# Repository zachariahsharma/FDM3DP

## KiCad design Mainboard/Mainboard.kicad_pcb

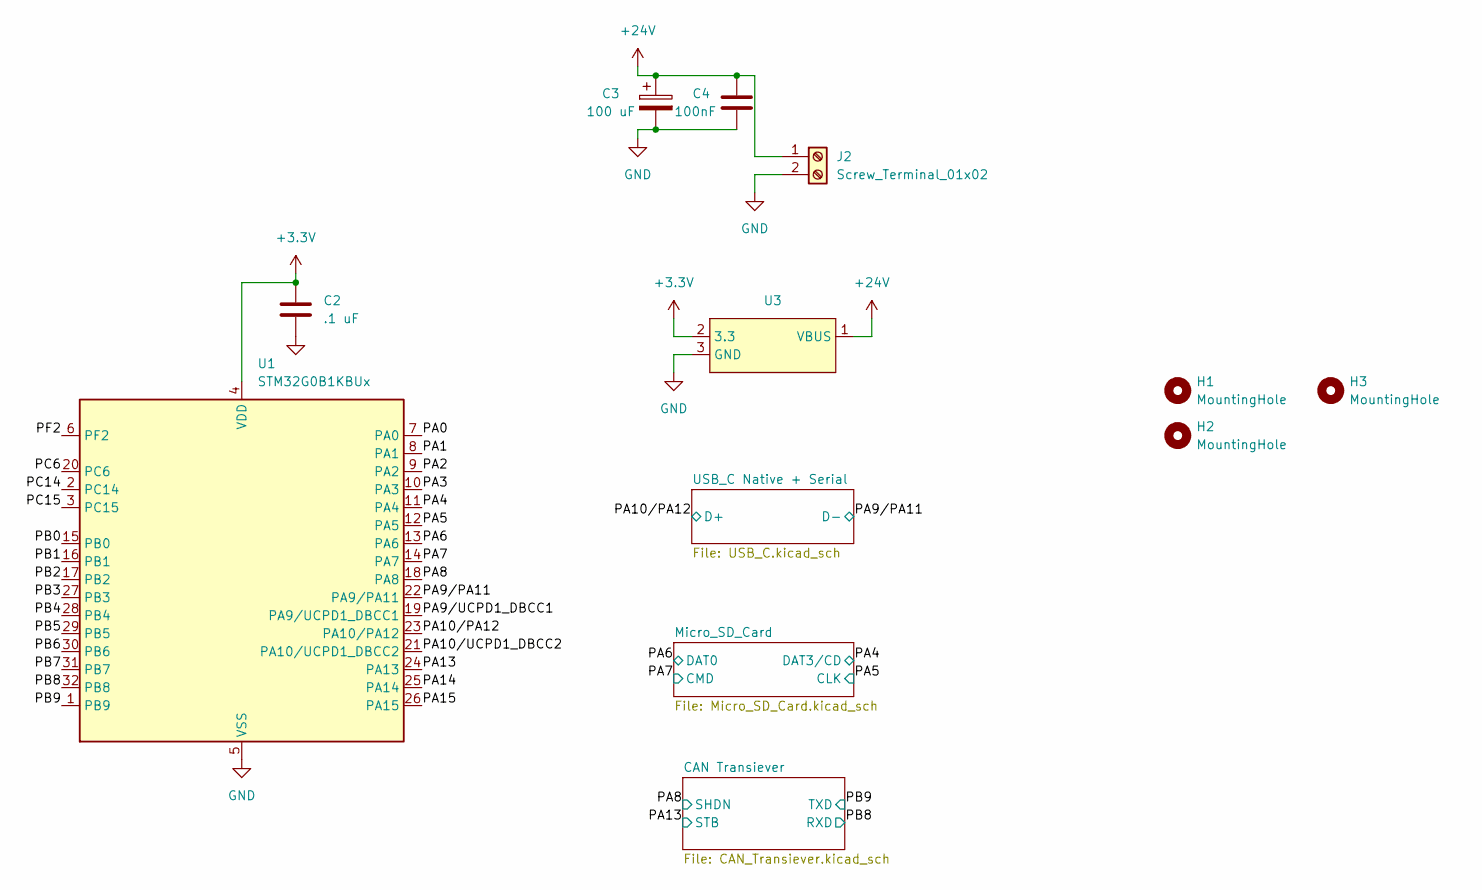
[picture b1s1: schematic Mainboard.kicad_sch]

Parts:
C2: .1 uF; C_0402_1005Metric; MPN GRM155R71C104KA88J
C3: 100 uF; CP_Radial_D8.0mm_P3.50mm; MPN 50ZLH100MEFC8X11.5
C4: 100nF; C_0402_1005Metric; MPN GRM155R71C104KA88J
H1, H2, H3: MountingHole; MountingHole_3mm
J2: Screw_Terminal_01x02; TerminalBlock_Phoenix_MKDS-1,5-2-5.08_1x02_P5.08mm_Horizont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; MPN 1715022
U1: STM32G0B1KBUx; QFN-32-1EP_5x5mm_P0.5mm_EP3.45x3.45mm; MPN STM32G0B1KBU6N
U3: Mini MP1584EN Buck Converter Module

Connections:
+3.3V: C2.1, U1.4 (VDD), U3.2 (3.3); also elsewhere on the board
+24V: C3.1, C4.1, J2.1, U3.1 (VBUS)
/PA0: U1.7 (PA0)
/PA1: U1.8 (PA1)
/PA2: U1.9 (PA2)
/PA3: U1.10 (PA3)
/PA4: U1.11 (PA4); also elsewhere on the board
/PA5: U1.12 (PA5); also elsewhere on the board
/PA6: U1.13 (PA6); also elsewhere on the board
/PA7: U1.14 (PA7); also elsewhere on the board
/PA8: U1.18 (PA8); also elsewhere on the board
/PA9/PA11: U1.22 (PA9/PA11); also elsewhere on the board
/PA9/UCPD1_DBCC1: U1.19 (PA9/UCPD1_DBCC1)
/PA10/PA12: U1.23 (PA10/PA12); also elsewhere on the board
/PA10/UCPD1_DBCC2: U1.21 (PA10/UCPD1_DBCC2)
/PA13: U1.24 (PA13); also elsewhere on the board
/PA14: U1.25 (PA14)
/PA15: U1.26 (PA15)
/PB0: U1.15 (PB0)
/PB1: U1.16 (PB1)
/PB2: U1.17 (PB2)
/PB3: U1.27 (PB3)
/PB4: U1.28 (PB4)
/PB5: U1.29 (PB5)
/PB6: U1.30 (PB6)
/PB7: U1.31 (PB7)
/PB8: U1.32 (PB8); also elsewhere on the board
/PB9: U1.1 (PB9); also elsewhere on the board
/PC6: U1.20 (PC6)
/PC14: U1.2 (PC14)
/PC15: U1.3 (PC15)
/PF2: U1.6 (PF2)
GND: C2.2, C3.2, C4.2, J2.2, U1.5 (VSS), U1.33 (VSS), U3.3 (GND); also elsewhere on the board

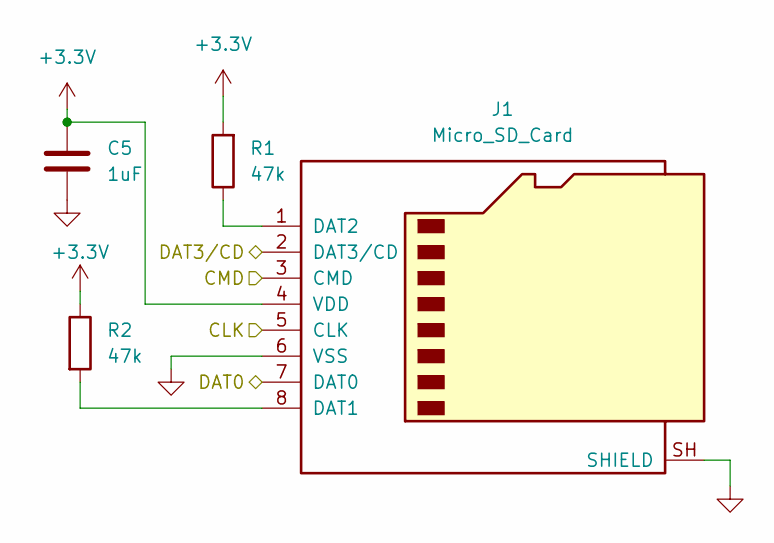
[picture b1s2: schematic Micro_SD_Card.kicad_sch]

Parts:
C5: 1uF; C_0805_2012Metric; MPN C0805C105K3RACTU
J1: Micro_SD_Card; microSD_HC_Hirose_DM3AT-SF-PEJM5; MPN DM3AT-SF-PEJM5
R1, R2: 47k; R_0402_1005Metric; MPN RC0402FR-0747KL

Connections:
+3.3V: C5.1, J1.4 (VDD), R1.2, R2.1; also elsewhere on the board
/PA4: J1.2 (DAT3/CD); also elsewhere on the board
/PA5: J1.5 (CLK); also elsewhere on the board
/PA6: J1.7 (DAT0); also elsewhere on the board
/PA7: J1.3 (CMD); also elsewhere on the board
GND: C5.2, J1.6 (VSS), J1.SH (SHIELD); also elsewhere on the board
unnamed: J1.8 (DAT1), R2.2
unnamed: J1.1 (DAT2), R1.1

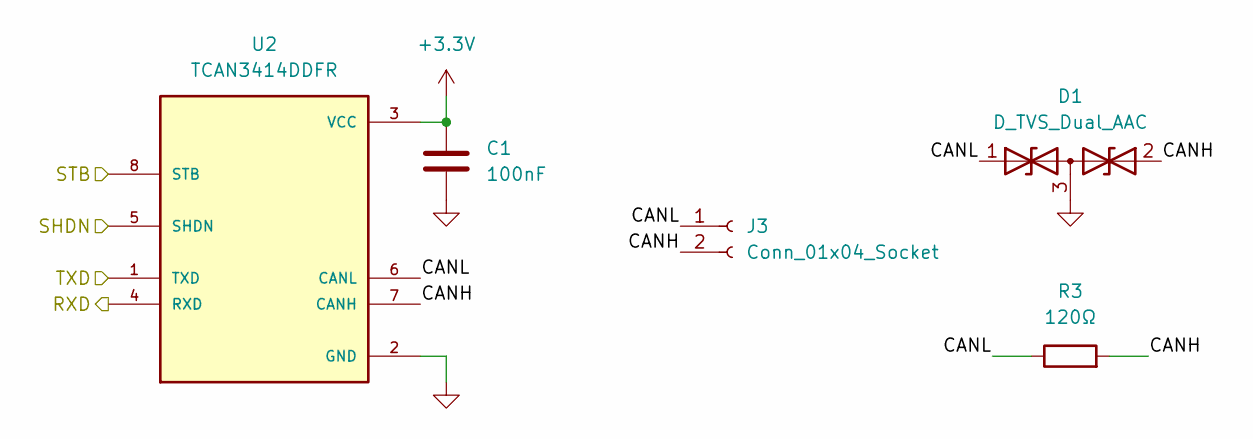
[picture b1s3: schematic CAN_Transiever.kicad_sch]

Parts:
C1: 100nF; C_0402_1005Metric; MPN GRM155R71C104KA88J
D1: D_TVS_Dual_AAC; SOT-23; MPN NUP2105LT1G
J3: Conn_01x04_Socket; PhoenixContact_MC_1,5_2-G-3.5_1x02_P3.50mm_Horizontal; MPN 1843990
R3: 120Ω; R_0402_1005Metric; MPN RC0402FR-07120RL
U2: TCAN3414DDFR; TSOT-23-8; MPN TCAN3414DDFR

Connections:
+3.3V: C1.1, U2.3 (VCC); also elsewhere on the board
/CAN Transiever/CANH: D1.2 (A2), J3.2, R3.2, U2.7 (CANH)
/CAN Transiever/CANL: D1.1 (A1), J3.1, R3.1, U2.6 (CANL)
/PA8: U2.5 (SHDN); also elsewhere on the board
/PA13: U2.8 (STB); also elsewhere on the board
/PB8: U2.4 (RXD); also elsewhere on the board
/PB9: U2.1 (TXD); also elsewhere on the board
GND: C1.2, D1.3 (common), U2.2 (GND); also elsewhere on the board

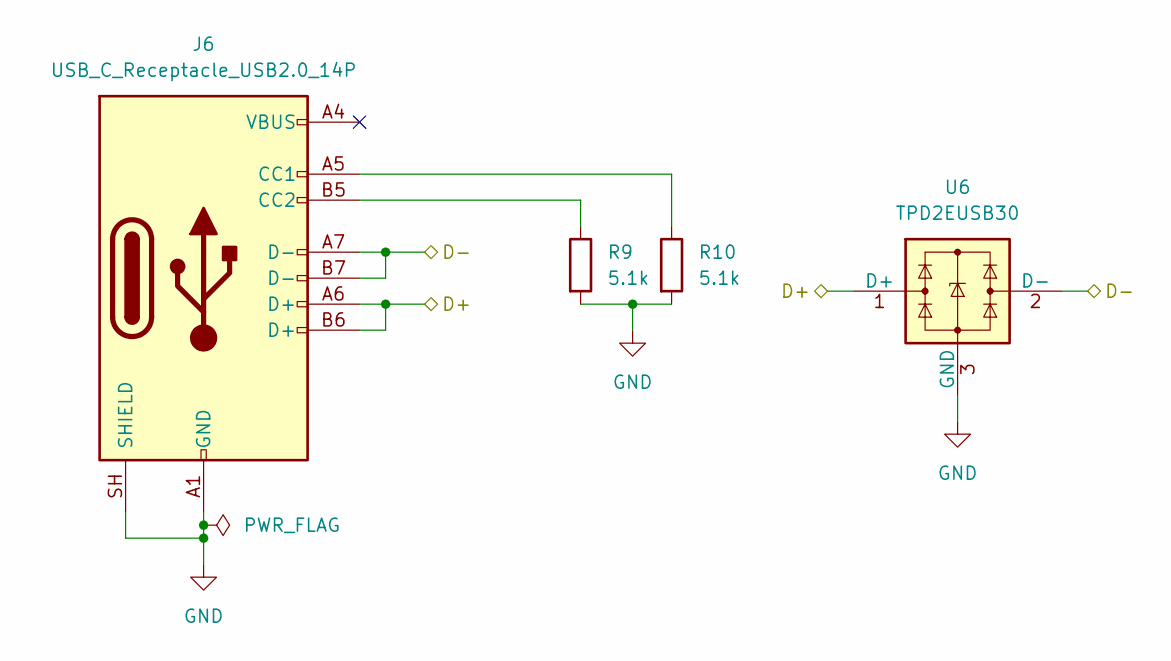
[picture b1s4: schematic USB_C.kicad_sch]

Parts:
J6: USB_C_Receptacle_USB2.0_14P; USB_C_Receptacle_GCT_USB4085; MPN USB4085-GF-A
R9, R10: 5.1k; R_0402_1005Metric; MPN RC0402FR-075K1L
U6: TPD2EUSB30; Texas_DRT-3; MPN TPD2EUSB30DRTR

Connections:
/PA9/PA11: J6.A7 (D-), J6.B7 (D-), U6.2 (D-); also elsewhere on the board
/PA10/PA12: J6.A6 (D+), J6.B6 (D+), U6.1 (D+); also elsewhere on the board
GND: J6.A1 (GND), J6.A12 (GND), J6.B1 (GND), J6.B12 (GND), J6.SH (SHIELD), R9.2, R10.2, U6.3 (GND); also elsewhere on the board
unnamed: J6.A5 (CC1), R10.1
unnamed: J6.B5 (CC2), R9.1

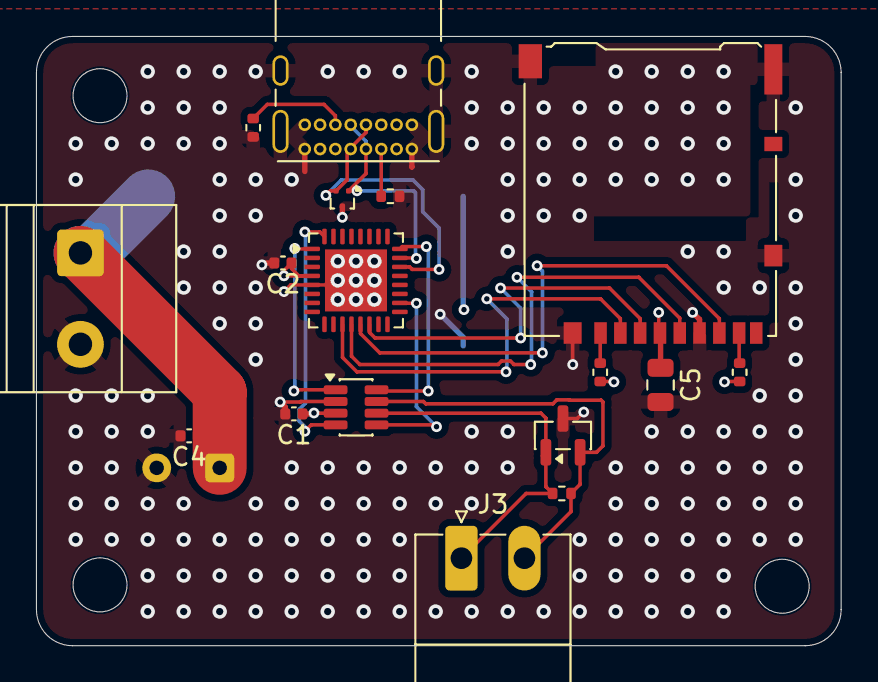
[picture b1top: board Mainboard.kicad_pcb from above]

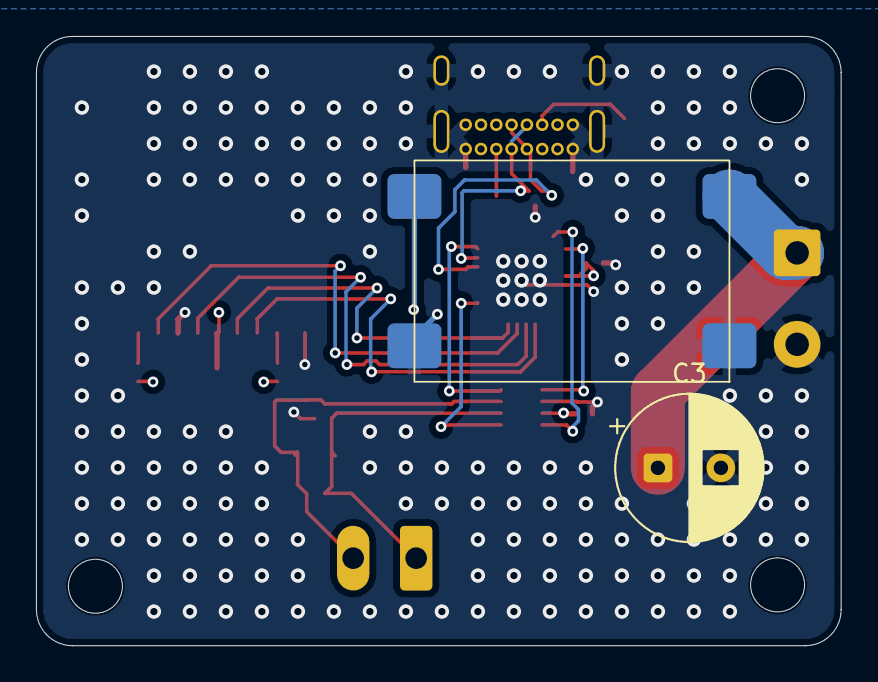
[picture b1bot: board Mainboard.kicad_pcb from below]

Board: 4 copper layers, 44.7 x 33.8 mm, 22 parts (2 on the bottom side), 19 nets.

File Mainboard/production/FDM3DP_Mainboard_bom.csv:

Designator,Footprint,Quantity,Value,LCSC Part #
"C1, C4",0402,2,100nF,KAM05FR71H104KH
C2,0402,1,.1 uF,KAM05FR71H104KH
C3,CP_Radial_D8.0mm_P3.50mm,1,100 uF,50ZLH100MEFC8X11.5
C5,0805,1,1uF,C0805C105K3RACTU
D1,SOT-23,1,D_TVS_Dual_AAC,NUP2105LT1G
J1,microSD_HC_Hirose_DM3AT-SF-PEJM5,1,Micro_SD_Card,DM3AT-SF-PEJM5
J2,"TerminalBlock_Phoenix_MKDS-1,5-2-5.08_1x02_P5.08mm_Horizontal",1,Screw_Terminal_01x02,1715022
J3,"PhoenixContact_MC_1,5_2-G-3.5_1x02_P3.50mm_Horizontal",1,Conn_01x04_Socket,1843990
J6,USB_C_Receptacle_GCT_USB4085,1,USB_C_Receptacle_USB2.0_14P,USB4085-GF-A
"R1, R2",0402,2,47k,RC0402FR-0747KL
"R10, R9",0402,2,5.1k,RC0402FR-075K1L
R3,0402,1,120Ω,RC0402FR-07120RL
U1,QFN-32-1EP_5x5mm_P0.5mm_EP3.45x3.45mm,1,STM32G0B1KBUx,STM32G0B1KBU6N
U2,TSOT-23-8,1,TCAN3414DDFR,TCAN3414DDFR
U3,Mini MP1584EN Buck Converter Module,1,~,
U6,Texas_DRT-3,1,TPD2EUSB30,TPD2EUSB30DRTR

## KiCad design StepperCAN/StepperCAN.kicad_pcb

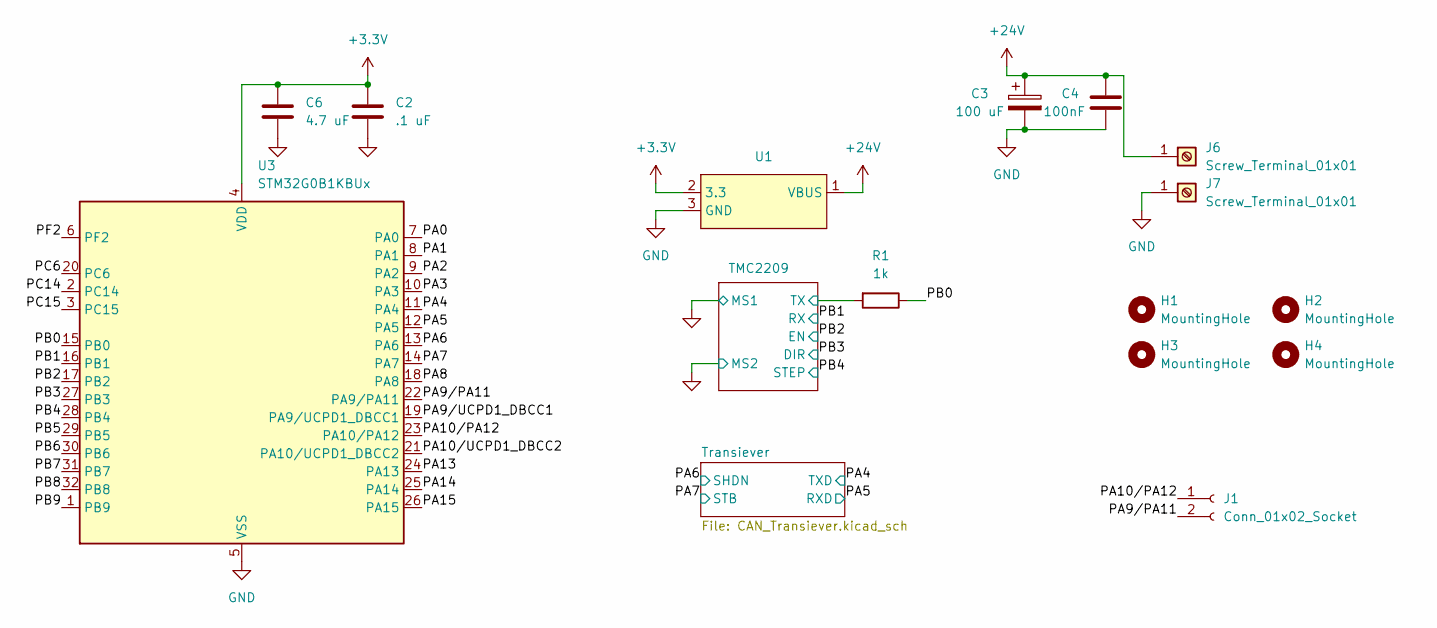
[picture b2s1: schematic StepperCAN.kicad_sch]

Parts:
C2: .1 uF; C_0402_1005Metric; MPN GRM155R71C104KA88J
C3: 100 uF; CP_Radial_D8.0mm_P3.50mm; MPN 50ZLH100MEFC8X11.5
C4: 100nF; C_0402_1005Metric; MPN GRM155R71C104KA88J
C6: 4.7 uF; C_0402_1005Metric; MPN CL05A475MO5NUNC
H1, H2, H3, H4: MountingHole; MountingHole_2.7mm_M2.5
J1: Conn_01x02_Socket; PinSocket_1x02_P2.54mm_Vertical
J6, J7: Screw_Terminal_01x01; M3 Screw Terminal
R1: 1k; R_0402_1005Metric; MPN RC0402FR-071KL
U1: Mini MP1584EN Buck Converter Module
U3: STM32G0B1KBUx; QFN-32-1EP_5x5mm_P0.5mm_EP3.45x3.45mm; MPN STM32G0B1KBU6N

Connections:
+3.3V: C2.1, C6.1, U1.2 (3.3), U3.4 (VDD); also elsewhere on the board
+24V: C3.1, C4.1, J6.1 (Pin_1_1), U1.1 (VBUS); also elsewhere on the board
/PA0: U3.7 (PA0)
/PA1: U3.8 (PA1)
/PA2: U3.9 (PA2)
/PA3: U3.10 (PA3)
/PA4: U3.11 (PA4); also elsewhere on the board
/PA5: U3.12 (PA5); also elsewhere on the board
/PA6: U3.13 (PA6); also elsewhere on the board
/PA7: U3.14 (PA7); also elsewhere on the board
/PA8: U3.18 (PA8)
/PA9/PA11: J1.2, U3.22 (PA9/PA11)
/PA9/UCPD1_DBCC1: U3.19 (PA9/UCPD1_DBCC1)
/PA10/PA12: J1.1, U3.23 (PA10/PA12)
/PA10/UCPD1_DBCC2: U3.21 (PA10/UCPD1_DBCC2)
/PA13: U3.24 (PA13)
/PA14: U3.25 (PA14)
/PA15: U3.26 (PA15)
/PB0: R1.1, U3.15 (PB0)
/PB1: R1.2, U3.16 (PB1); also elsewhere on the board
/PB2: U3.17 (PB2); also elsewhere on the board
/PB3: U3.27 (PB3); also elsewhere on the board
/PB4: U3.28 (PB4); also elsewhere on the board
/PB5: U3.29 (PB5)
/PB6: U3.30 (PB6)
/PB7: U3.31 (PB7)
/PB8: U3.32 (PB8)
/PB9: U3.1 (PB9)
/PC6: U3.20 (PC6)
/PC14: U3.2 (PC14)
/PC15: U3.3 (PC15)
/PF2: U3.6 (PF2)
GND: C2.2, C3.2, C4.2, C6.2, J7.1 (Pin_1_1), U1.3 (GND), U3.5 (VSS), U3.33 (VSS); also elsewhere on the board

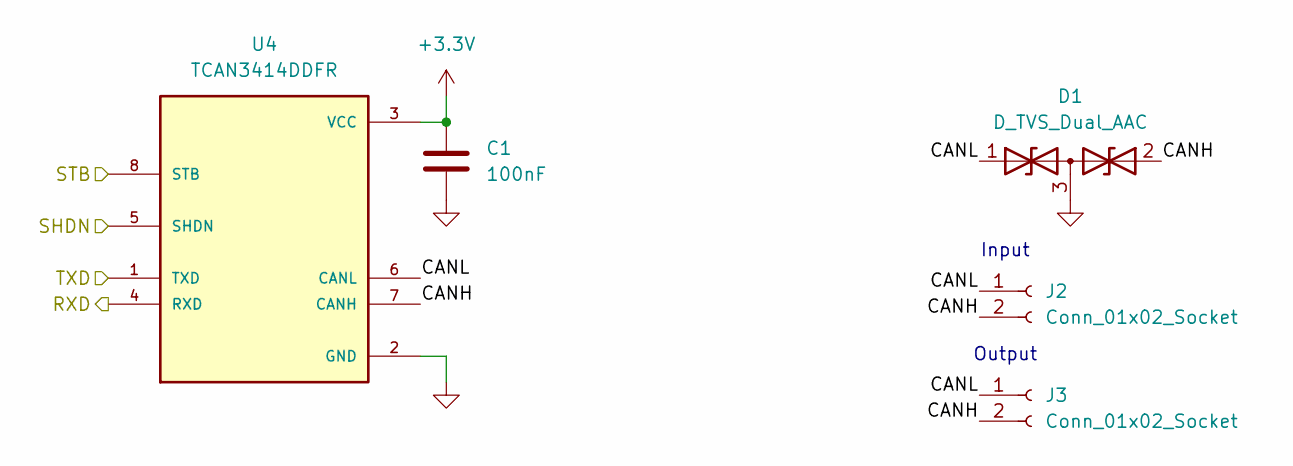
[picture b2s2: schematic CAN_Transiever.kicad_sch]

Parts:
C1: 100nF; C_0402_1005Metric; MPN GRM155R71C104KA88J
D1: D_TVS_Dual_AAC; SOT-23; MPN NUP2105LT1G
J2, J3: Conn_01x02_Socket; PhoenixContact_MC_1,5_2-G-3.5_1x02_P3.50mm_Horizontal
U4: TCAN3414DDFR; TSOT-23-8; MPN TCAN3414DDFR

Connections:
+3.3V: C1.1, U4.3 (VCC); also elsewhere on the board
/PA4: U4.1 (TXD); also elsewhere on the board
/PA5: U4.4 (RXD); also elsewhere on the board
/PA6: U4.5 (SHDN); also elsewhere on the board
/PA7: U4.8 (STB); also elsewhere on the board
/Transiever/CANH: D1.2 (A2), J2.2, J3.2, U4.7 (CANH)
/Transiever/CANL: D1.1 (A1), J2.1, J3.1, U4.6 (CANL)
GND: C1.2, D1.3 (common), U4.2 (GND); also elsewhere on the board

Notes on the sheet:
Output
Input

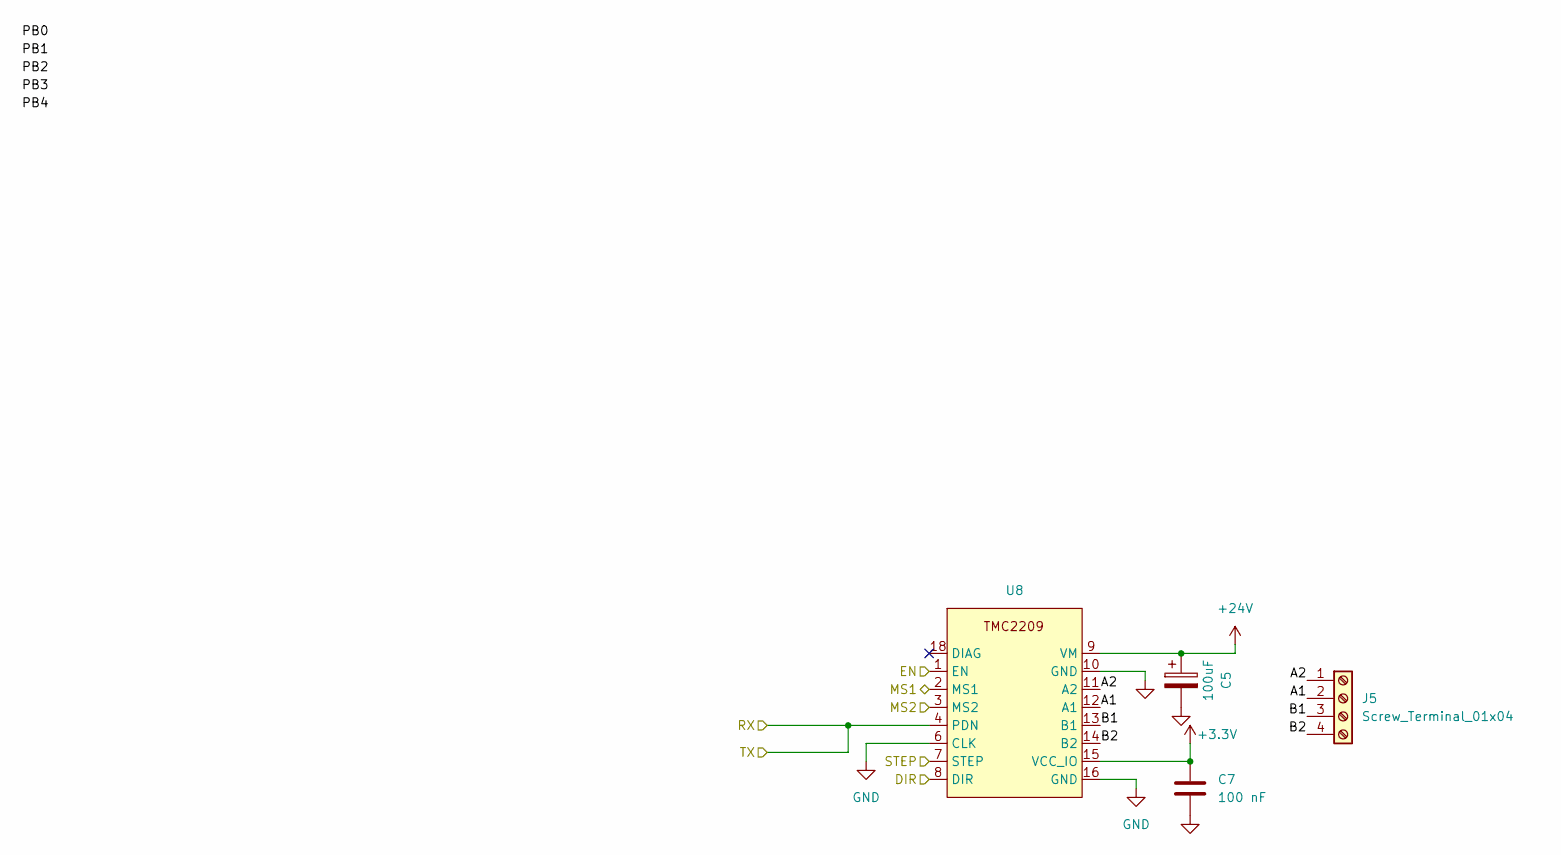
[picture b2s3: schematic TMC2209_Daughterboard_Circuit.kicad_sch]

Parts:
C5: 100uF; CP_Radial_D8.0mm_P3.50mm
C7: 100 nF; C_0402_1005Metric; MPN GRM155R71C104KA88J
J5: Screw_Terminal_01x04; TerminalBlock_Phoenix_MKDS-1,5-4-5.08_1x04_P5.08mm_Horizont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
U8: TMC2209 V1.3

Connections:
+3.3V: C7.1, U8.15 (VCC_IO); also elsewhere on the board
+24V: C5.1, U8.9 (VM); also elsewhere on the board
/PB1: U8.4 (PDN); also elsewhere on the board
/PB2: U8.1 (EN); also elsewhere on the board
/PB3: U8.8 (DIR); also elsewhere on the board
/PB4: U8.7 (STEP); also elsewhere on the board
/TMC2209/A1: J5.2, U8.12 (A1)
/TMC2209/A2: J5.1, U8.11 (A2)
/TMC2209/B1: J5.3, U8.13 (B1)
/TMC2209/B2: J5.4, U8.14 (B2)
GND: C5.2, C7.2, U8.2 (MS1), U8.3 (MS2), U8.6 (CLK), U8.10 (GND), U8.16 (GND); also elsewhere on the board

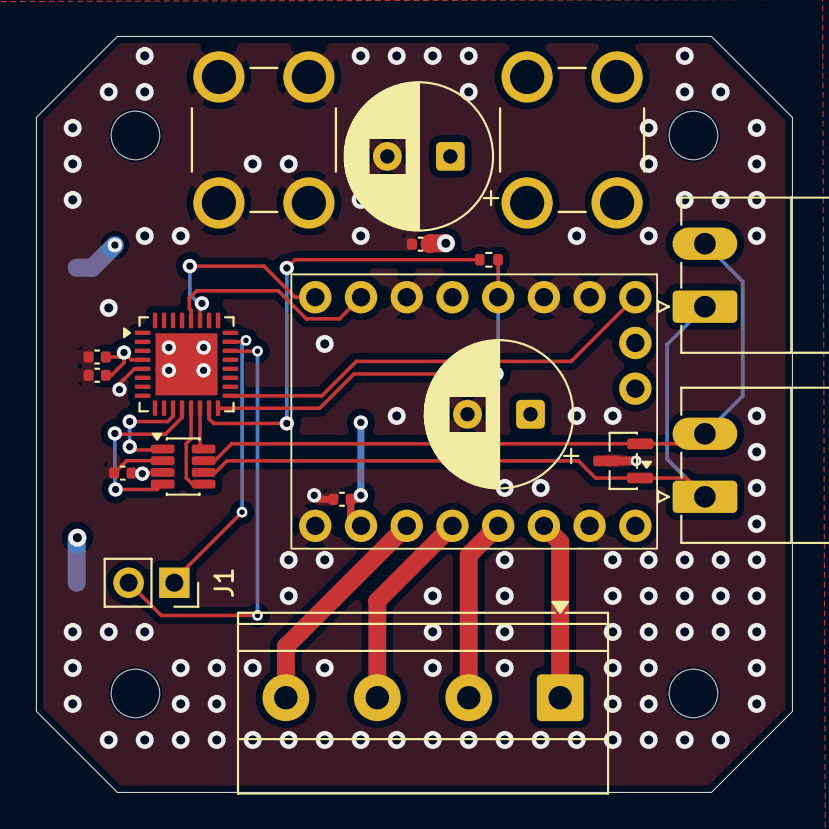
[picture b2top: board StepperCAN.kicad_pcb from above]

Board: 4 copper layers, 42.0 x 42.0 mm, 23 parts (1 on the bottom side), 20 nets.
